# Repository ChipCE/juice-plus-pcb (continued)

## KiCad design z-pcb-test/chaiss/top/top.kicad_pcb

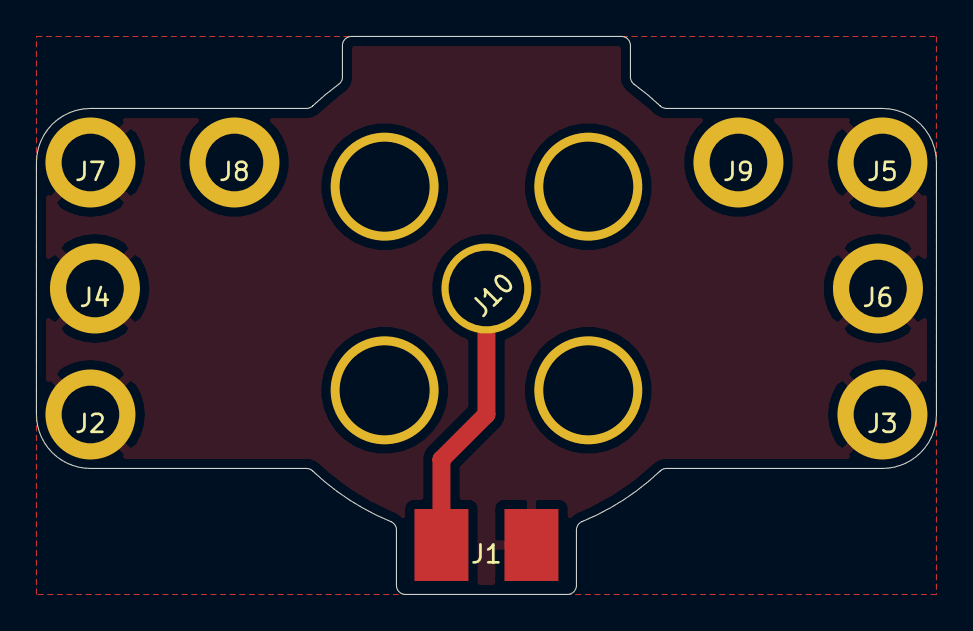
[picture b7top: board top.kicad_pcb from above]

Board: 2 copper layers, 50.0 x 31.0 mm, 10 parts (0 on the bottom side), 2 nets.

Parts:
J1: Conn_01x02_Female; chaiss-solder-pad
J2, J3, J4, J5, J6, J7, J8, J9: Conn_01x01_Female; chaiss_m3_mounting_hole
J10: Conn_01x01_Female; chaiss-dragon-top

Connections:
unnamed: J1.1, J10.1
unnamed: J1.2, J2.1, J3.1, J4.1, J5.1, J6.1, J7.1

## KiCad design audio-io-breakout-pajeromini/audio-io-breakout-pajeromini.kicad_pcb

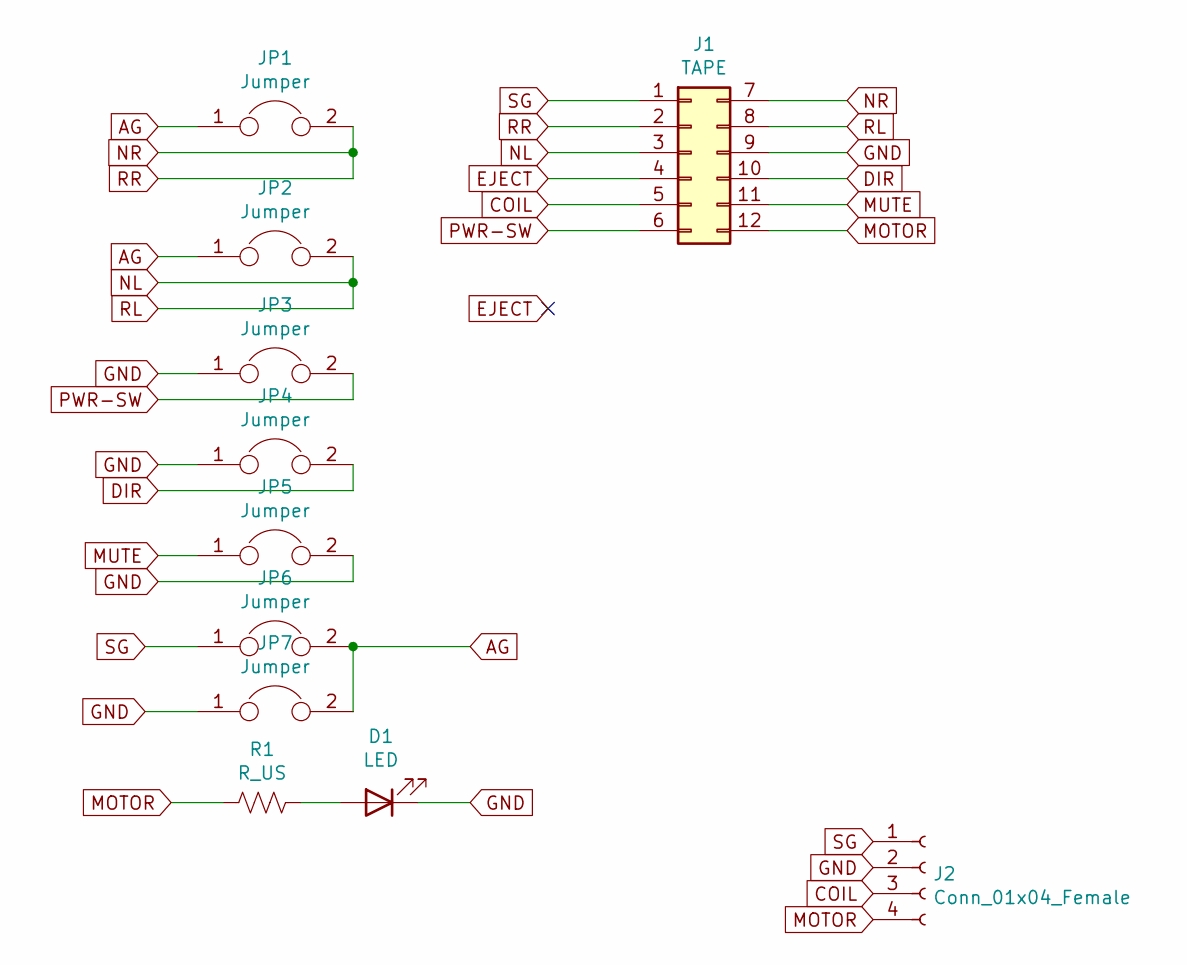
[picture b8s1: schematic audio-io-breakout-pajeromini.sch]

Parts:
D1: LED; LED_0805_2012Metric_Pad1.15x1.40mm_HandSolder
J1: TAPE; connector-12p-offset
J2: Conn_01x04_Female; JST_XH_S4B-XH-A-1_1x04_P2.50mm_Horizontal
JP1, JP2, JP3, JP4, JP5, JP6, JP7: Jumper; SolderJumper-2_P1.3mm_Open_RoundedPad1.0x1.5mm
R1: R_US; R_0805_2012Metric_Pad1.20x1.40mm_HandSolder

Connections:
AG: JP1.1, JP2.1, JP6.2, JP7.2
COIL: J1.5, J2.3
DIR: J1.10, JP4.2
EJECT: J1.4
GND: D1.1 (K), J1.9, J2.2, JP3.1, JP4.1, JP5.2, JP7.1
MOTOR: J1.12, J2.4, R1.2
MUTE: J1.11, JP5.1
NL: J1.3, J1.8, JP2.2
NR: J1.2, J1.7, JP1.2
unnamed: D1.2 (A), R1.1
PWR-SW: J1.6, JP3.2
SG: J1.1, J2.1, JP6.1

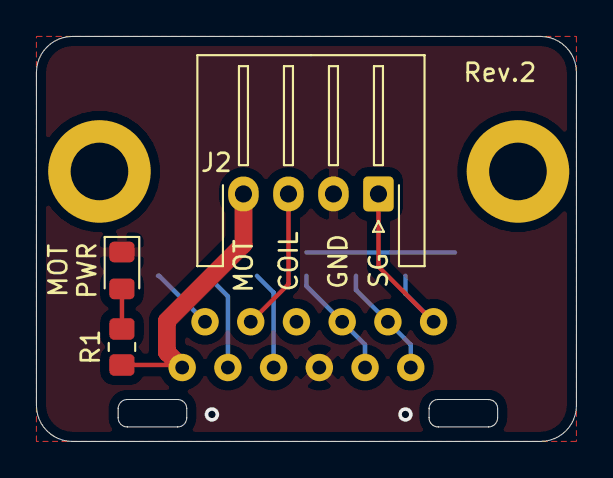
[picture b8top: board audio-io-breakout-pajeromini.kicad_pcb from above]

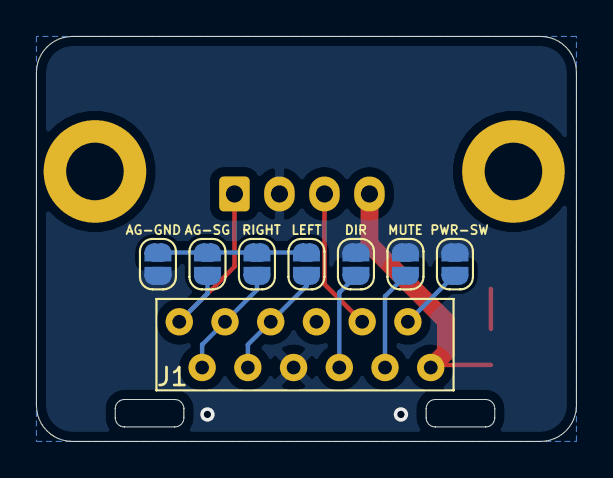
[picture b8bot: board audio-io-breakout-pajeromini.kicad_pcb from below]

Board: 2 copper layers, 30.0 x 22.5 mm, 11 parts (8 on the bottom side), 11 nets.

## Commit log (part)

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2021-08-12 init
2022-03-27 sync
2022-11-10 sync!
2023-03-08 sync2
